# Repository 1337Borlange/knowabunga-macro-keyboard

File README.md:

# Knowabunga 2024 - macro keyboard 

In this repo you will find QMK keyboard files for the knowabunga keyboard made in Borlänge 2024. As well as all Kicad design files for the PCB itself.

## Building and flashing firmware

To start you are going to need QMK to be setup on the machine. To do this head over to the official guide at [https://docs.qmk.fm/newbs_getting_started](https://docs.qmk.fm/newbs_getting_started).

Once QMK is installed, copy the folder `keyboards/macroblg` into `<qmk_source>/keyboards/`

> Running the following command will print the location of your QMK source directory  
 `qmk env QMK_HOME`

To build the firmware run:
```
qmk compile -kb macroblg -km default
```

This will generate a .bin and .hex file with the firmware. This firmware is designed to work with the Arduino ProMicro which is the controller used on the board.

Once built the firmware can be uploaded. Plug the ProMicro into your computer and run:
```
qmk flash -kb macroblg -km default
```

The on screen instructions will tell you it is waiting for the controller. To put it into programming mode, push once on the reset button located on the board.

If everything worked a progressbar should show up as the firmware is uploaded.

Congratz, you just flashed your first firmware.

## Changing keymap

In the `macroblg/keymaps/default/keymap.c` file you will find the layout specification, this describes what keycodes should be sent for each key. Right now the letters a-h are used (*KC_A - KC_H* respectivly) but you can change these to anything on this list [https://docs.qmk.fm/keycodes](https://docs.qmk.fm/keycodes).

Once changed: save the file, rebuild and reupload using the same instructions as above.,

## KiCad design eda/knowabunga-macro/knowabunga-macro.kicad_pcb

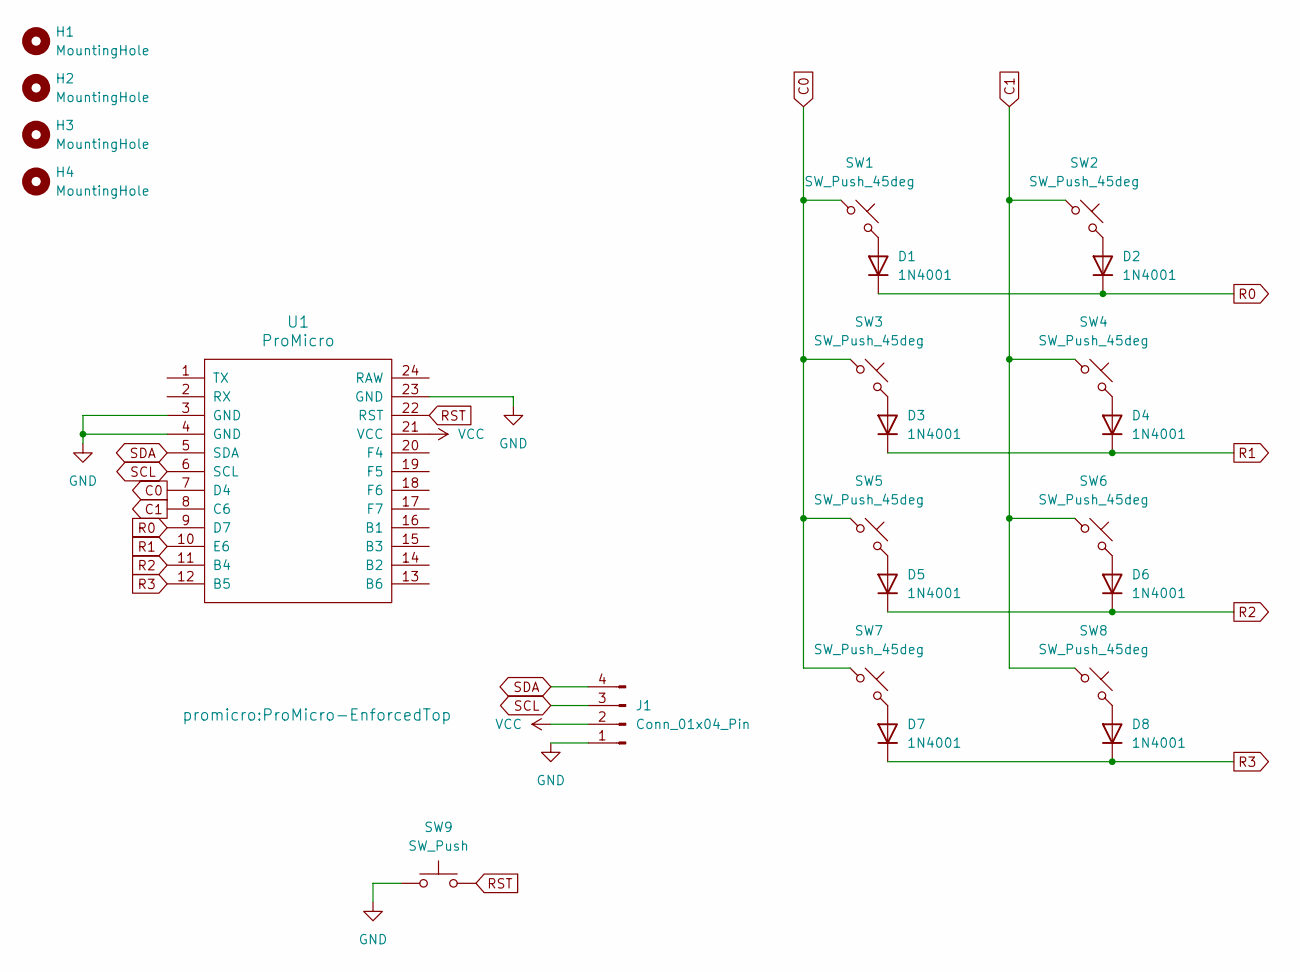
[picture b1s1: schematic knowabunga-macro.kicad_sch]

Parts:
D1, D2, D3, D4, D5, D6, D7, D8: 1N4001; D_DO-41_SOD81_P10.16mm_Horizontal
H1, H2, H3, H4: MountingHole; MountingHole_3.2mm_M3
J1: Conn_01x04_Pin; PinHeader_1x04_P2.54mm_Vertical
SW1, SW2, SW3, SW4, SW5, SW6, SW7, SW8: SW_Push_45deg; SW_Cherry_MX_1.00u_PCB
SW9: SW_Push; SW_PUSH_6mm
U1: ProMicro; ProMicro-EnforcedTop

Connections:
C0: SW1.1, SW3.1, SW5.1, SW7.1, U1.7 (D4)
C1: SW2.1, SW4.1, SW6.1, SW8.1, U1.8 (C6)
GND: J1.1, SW9.1, U1.3 (GND), U1.4 (GND), U1.23 (GND); also elsewhere on the board
unnamed: D1.2 (A), SW1.2
unnamed: D2.2 (A), SW2.2
unnamed: D3.2 (A), SW3.2
unnamed: D4.2 (A), SW4.2
unnamed: D5.2 (A), SW5.2
unnamed: D6.2 (A), SW6.2
unnamed: D7.2 (A), SW7.2
unnamed: D8.2 (A), SW8.2
R0: D1.1 (K), D2.1 (K), U1.9 (D7)
R1: D3.1 (K), D4.1 (K), U1.10 (E6)
R2: D5.1 (K), D6.1 (K), U1.11 (B4)
R3: D7.1 (K), D8.1 (K), U1.12 (B5)
RST: SW9.2, U1.22 (RST); also elsewhere on the board
SCL: J1.3, U1.6 (SCL)
SDA: J1.4, U1.5 (SDA)
VCC: J1.2, U1.21 (VCC)

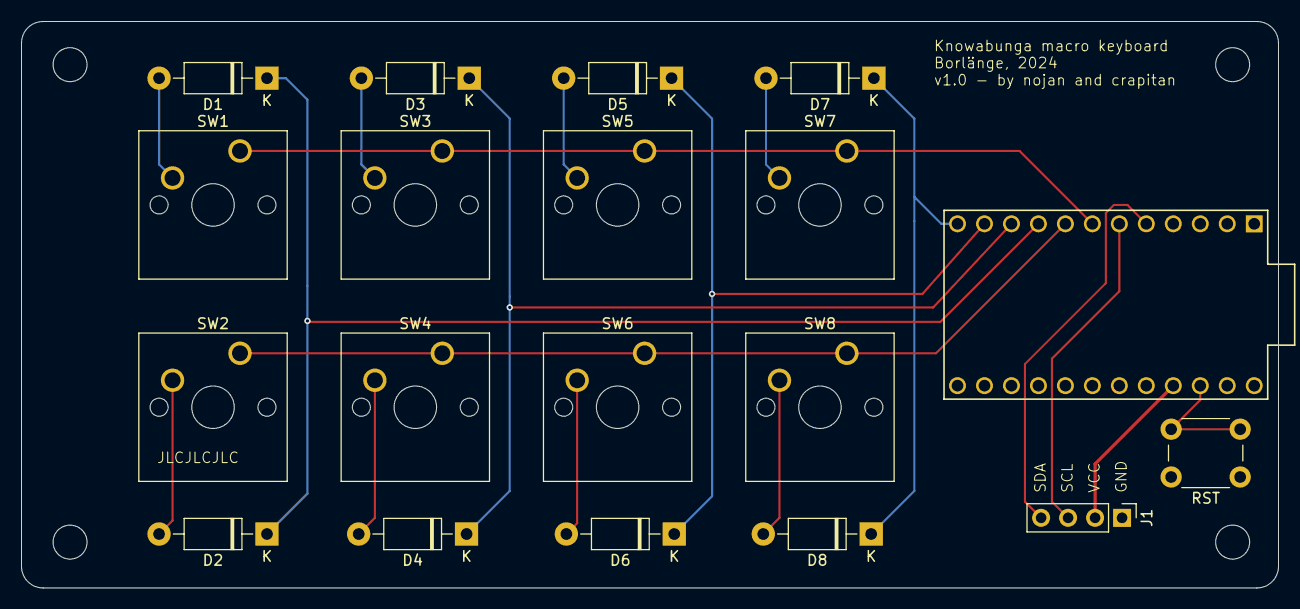
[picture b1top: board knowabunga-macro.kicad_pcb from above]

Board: 2 copper layers, 118.4 x 53.3 mm, 23 parts (0 on the bottom side), 19 nets.

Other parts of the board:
RST: SW_Push; SW_PUSH_6mm

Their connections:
GND: RST.1; also elsewhere on the board
RST: RST.2; also elsewhere on the board

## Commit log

2024-10-19 Add README and keyboard files
2024-10-19 Add eda files and models
